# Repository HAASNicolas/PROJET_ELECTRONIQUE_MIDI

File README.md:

# PROJET_ELECTRONIQUE_MIDI
## Participants
* Lina Bachir
* Nicolas Haas
* Tanoh Koffi

## Code C
```C
int main (void)
{
  printf(C);
}
```

## Commandes github
Sous window: Dans le répertoire faire clique droit 'ouvrir un git bach', puis aller dans le bon dossier (si c'est pas déjà le cas):

Sous linux: Ouvrir un terminal, puis aller dans le bon dossier. Par exemple :
```
cd Documents/git_1A/PROJET_ELECTRONIQUE_MIDI/
```

Pour créer un nouveau répertoire git:
```
git config --global user.name "Pseudo git ou Nom Prénom"
git config --global user.email "Votre e-mail"
```
Testez
```
git clone adresse_du_git
```
Si git clone marche: Vous avez fini !
Sinon si git clone ne marche pas:
```
ssh-keygen
```
Faites Entrer plusieurs fois, puis copier l'adresse /c/....pub (example: /c/Users/user_name/.ssh/id_ed25519.pub)
```
cat adresse_pub_copié_ci_dessus
```
Copier ssh key, puis Ajouter ssh key sur github.com -> setting -> sshkey
```
git clone adresse_du_git
```

Pour récupérer les modifications distantes :
```
git pull
```

Pour pousser des modifications locales
```
git add .
git commit -m "Message à remplacer"
git push
```
# Rapport projet 
## Introduction

Notre projet consiste en la création d’un contrôleur MIDI, un dispositif électronique conçu pour interagir avec divers instruments et logiciels musicaux. Le contrôleur comporte une variété de boutons, de potentiomètres et de curseurs, offrant un contrôle précis et intuitif de nombreux aspects de la production musicale, tels que le volume, les effets, et la modulation.

La conception du contrôleur inclut l’intégration de plusieurs capteurs pour détecter les actions de l’utilisateur, qui sont ensuite traduites en signaux MIDI. Ces signaux sont transmis à un ordinateur ou un autre appareil musical via une interface MIDI, permettant un contrôle en temps réel de la musique.

Le développement de ce contrôleur MIDI inclut la mise en œuvre d’une carte électronique centrale, qui gère les signaux provenant des différents capteurs, ainsi qu’une interface de sortie pour la communication avec les appareils externes.

## objectif

L'objectif de notre projet est de concevoir un contrôleur MIDI fonctionnel et intuitif, permettant aux musiciens et aux producteurs de gérer et de manipuler leurs compositions musicales de manière fluide. 
Nous cherchons à créer un dispositif qui permette un contrôle précis et efficace des éléments clés de la production musicale, tels que le volume, les effets, et la modulation.

* Implémentation du MIDI classique

  Nous voulons une compatibilité universelle avec beaucoup d'instruments et de logiciels musicaux en adoptant le protocole MIDI standard. Notre contrôleur sera conçu pour envoyer et recevoir des messages MIDI de façon fiable, facilitant ainsi son intégration dans diverses configurations musicales.

* Support du MIDI USB via USB-C

  Notre objectif est d'incorporer une interface MIDI moderne utilisant un port USB-C, permettant une connexion simple et efficace avec des ordinateurs et autres appareils prenant en charge l'USB. Cela englobera la transmission de données MIDI ainsi que l'alimentation du contrôleur.

* Autonomie sur batterie rechargeable

  Nous planifions de développer un contrôleur fonctionnant sur une batterie rechargeable pour maximiser la portabilité et la flexibilité d'utilisation. La batterie sera rechargeable via USB-C, offrant ainsi aux utilisateurs la possibilité de jouer sans être dépendant d'une source d'alimentation fixe.

* Inspirations et benchmarking

  Nous nous baserons sur des modèles de référence tels que l'Intech Studio PBF4, le Faderfox MX12 pour l'ergonomie et l'AKAI MIDIMIX pour sa disposition efficace. Ces produits nous serviront de guide dans le développement de notre contrôleur.

* Cahier des charges:

* Planning des séances

* Schéma global du projet

## PCB 

Dans cette partie de ce rapport, nous donnerons un aperçu complet de l'architecture et des composants du PCB de ce contrôleur MIDI.
On cherchera donc ici à comprendre le rôle des composants sur ce PCB et leur disposition.
Concernant le Microcontrôleur, ici le STM 32 KBTX, il est le centre du contrôleur MIDI. Son but ici est de gérer les entrées venues des boutons et potentiomètres, de traiter ces informations et d’envoyer les messages MIDI appropriés via les interfaces MIDI ou USB.

Quant aux Régulateurs de tension, ils assurent une tension stable pour alimenter les différents composants du circuit, par exemple, fournir 5V pour le microcontrôleur et 3.3V pour certains capteurs ou circuits.

On a aussi utilisé des Condensateurs pour filtrer les signaux, déparasiter les lignes d'alimentation et stabiliser les tensions. Ils sont essentiels pour réduire le bruit électronique et maintenir la stabilité des signaux. Ils sont dispersés autour du microcontrôleur et près des régulateurs de tension, souvent à proximité des broches d'alimentation pour optimiser leur efficacité. De plus, avec les Résistances, on parviendra à Limiter le courant, ajuster les niveaux de tension et effectuer des fonctions pull-up/pull-down sur les lignes de signal, elles sont quant à elles Connectées en série avec les boutons et situées près du microcontrôleur pour les pull-ups/pull-downs.

Le Connecteur MIDI utilisé ici va servir d’interface afin de connecter le contrôleur MIDI à d'autres dispositifs MIDI. Ce connecteur permet donc la communication des données MIDI. Un autre type de connecteur utilisé est le Connecteur USB qui va Permettre la connexion du contrôleur à un ordinateur pour la transmission de données MIDI et l'alimentation.

Les Traces, Les lignes rouges et bleues sur le schéma représentent les connexions électriques entre les composants. Les rouges sont sur la couche supérieure du PCB, et les bleues sur la couche inférieure. Elles sont connectées entre les différentes couches du PCB à l’aide des Vias, qui assurent ainsi une interconnexion entre les couches du PCB. Les potentiomètres, eux, capturent les entrées de l'utilisateur. Chaque potentiomètre envoie en effet un signal spécifique au microcontrôleur.

En outre, Le microcontrôleur central gère les entrées venues des boutons et les interfaces MIDI/USB. Les régulateurs de tension, condensateurs et résistances assurent la stabilité du circuit et les connecteurs MIDI et USB permettent la communication avec d'autres dispositifs MIDI et des ordinateurs.
En résumé, lorsqu'on modifie la position d’un potentiomètre du contrôleur MIDI, le microcontrôleur détecte ce changement et identifie le potentiomètre en question. Il génère ensuite un message MIDI avec les informations appropriées (comme la note et la vélocité). Ce message est transmis soit via le connecteur MIDI DIN à d'autres appareils MIDI, soit via USB à un ordinateur.

## Résultats
Nous avons réussi à faire fonctionner la carte, et a lui faire envoyer, via l'USART, des trames MIDI correspondants aux valeurs des potentiomètres.

Voici les valeurs que renvoient un des potentiomètres linéaire et un des potentiomètres rond. C'est valeurs doivent être comprise entre 0 et 127, car en MIDI on la code sur 7 bits.
Sel est le numéro transmis aux 4 MUX analogiques.

La carte regarde en boucle la valeur des potentiomètres. Si la valeur change, alors une trame MIDI est envoyée.

Comme l'ADC fait 4 conversions à la fois, nous pouvons voir 4 trames MIDI qui ce suivent:

Chaque trame comporte 3 octets, ayant chacun leur bit de start à 0.
* Le 1er octet et l'identifiant ici 0x1A
* Le 2e est le numéro du potentiomètre ici 24
* Le 3e et dernier est la valeur du potentiomètre (ici 30) codée sur 7 bits (donc le MSB qui se situe à droite est toujours à 0)

On remarque que les curseurs sont espacés de 9 bits et d'une durée de 78us. Ce qui est en accord avec notre programme que nous avons configuré pour émettre à une vitesse de 115200 bauds.

## Code

Voici le diagramme de notre code:

## Les difficultés rencontrées

* Lors de schéma afain d'avoir les bonnes valeurs des résistances et condensateurs.
* Le routage nous a aussi appris qu'il faut mettre des composants de protections, ainsi que le BMS pour la recharge de la batterie.
* Dans le routage, qui nous ont permis d'apprendre les bonnes pratiques.
* L'USART du STM32 ne voulait pas fonctionner en Half-Duplex, on a donc dû le mettre en Asynchronous. Nous avons donc la broche TX qui ne sert à rien.
* Pour le soudage de composants CMS, car il faut être précis.

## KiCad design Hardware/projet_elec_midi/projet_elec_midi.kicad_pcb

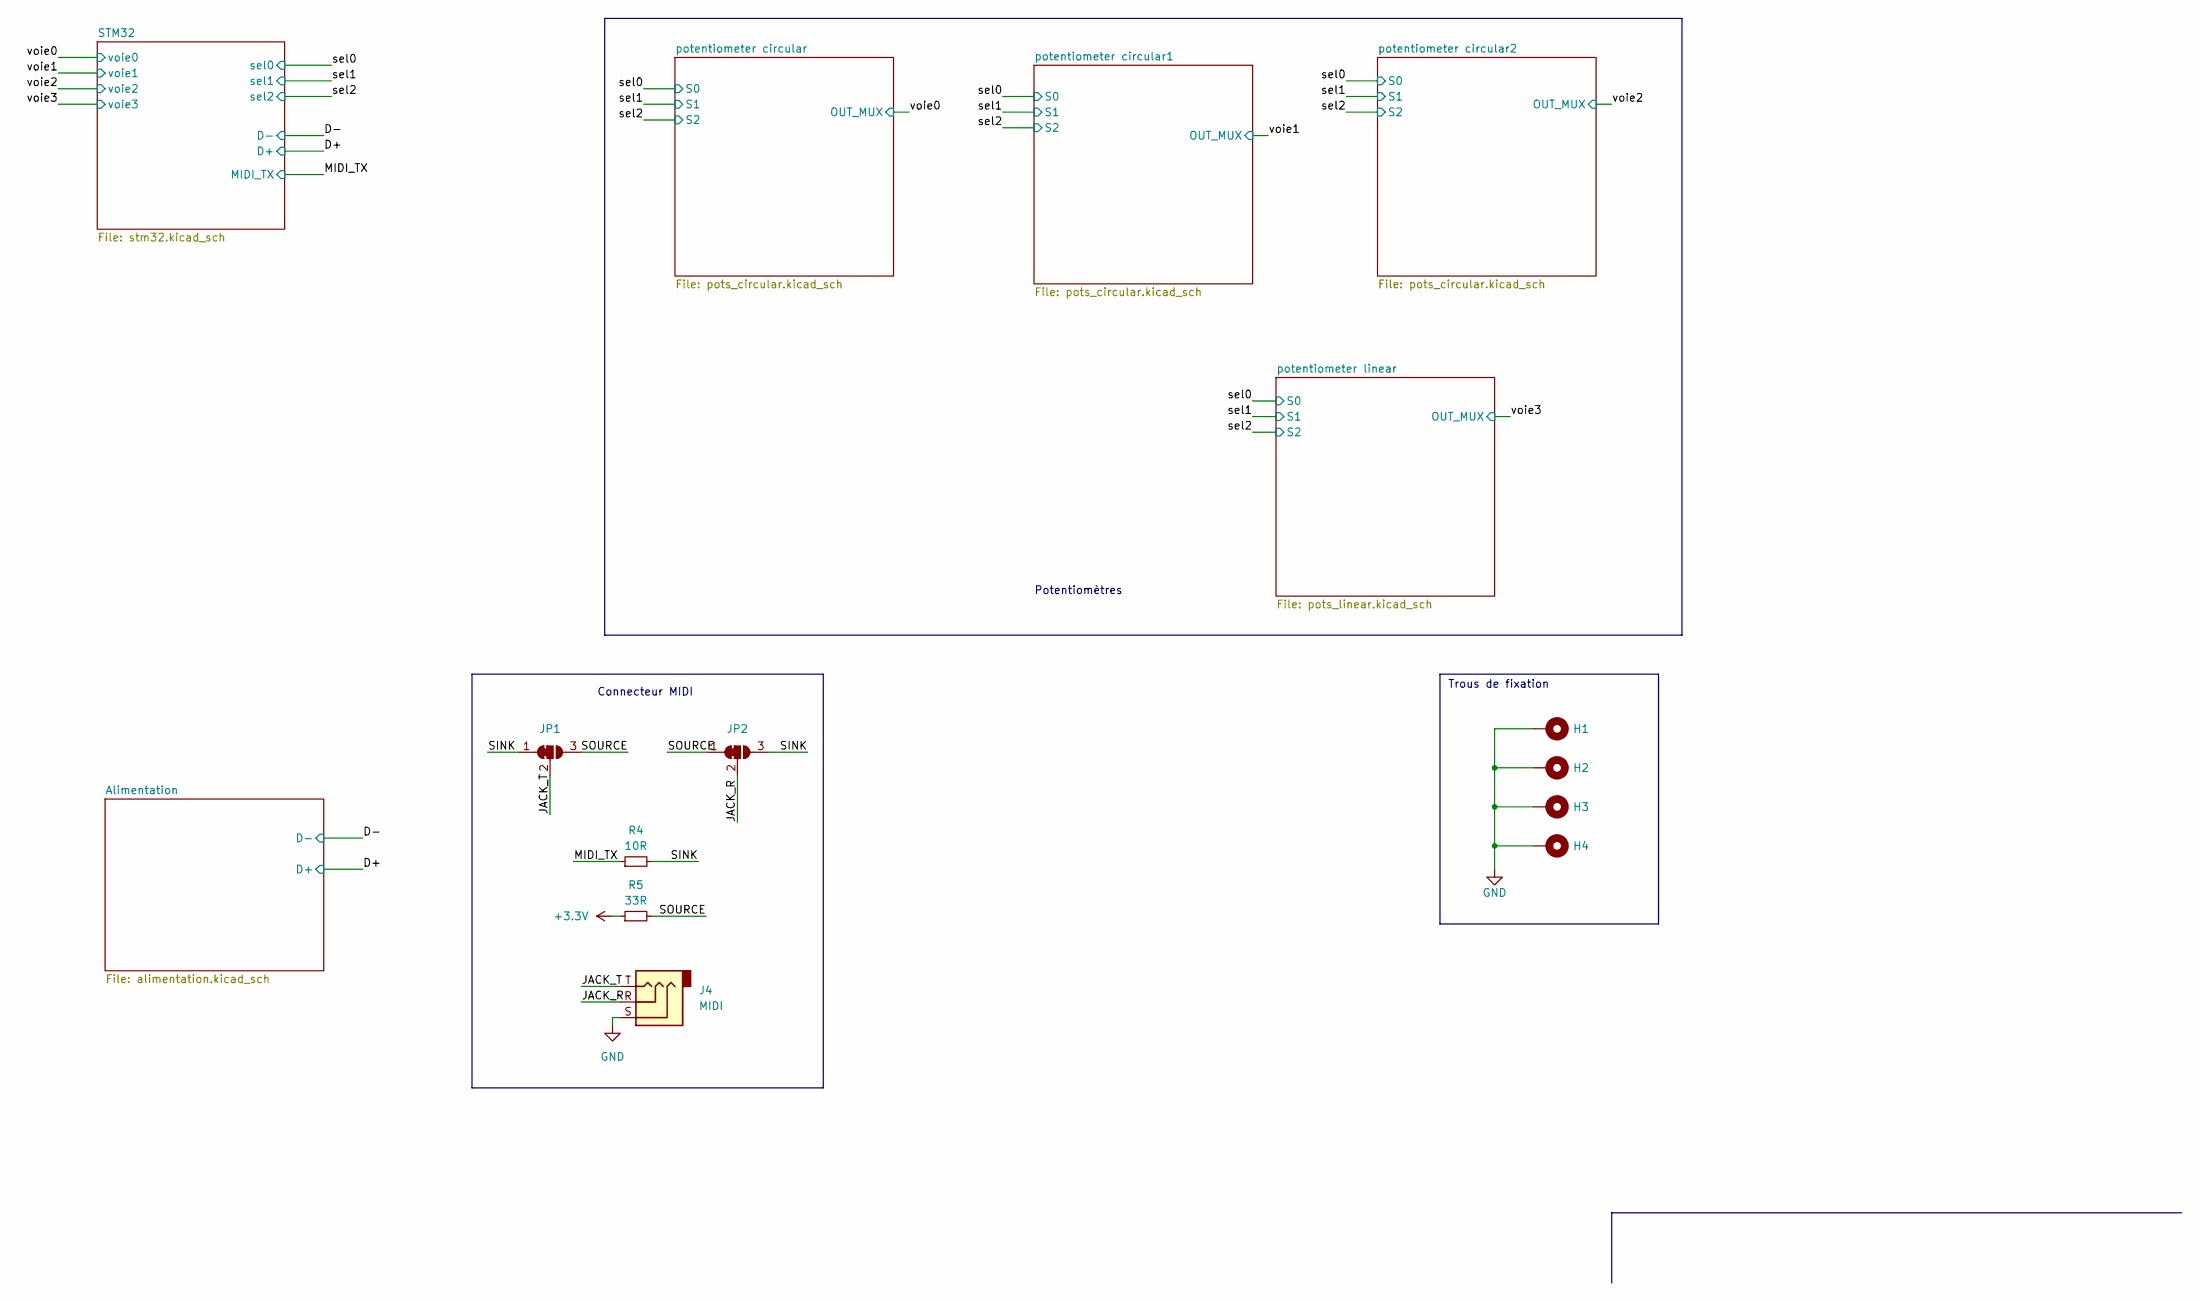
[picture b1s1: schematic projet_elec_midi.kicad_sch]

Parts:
H1, H2, H3, H4: MountingHole_Pad; MountingHole_3.2mm_M3_Pad_Via
J4: MIDI; Jack_3.5mm_CUI_SJ-3523-SMT_Horizontal
JP1, JP2: SolderJumper_3_Bridged12; SolderJumper-3_P1.3mm_Bridged12_RoundedPad1.0x1.5mm
R4: 10R; R_0805_2012Metric
R5: 33R; R_0805_2012Metric

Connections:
+3.3V: R5.1; also elsewhere on the board
/JACK_R: J4.R, JP2.2 (C)
/JACK_T: J4.T, JP1.2 (C)
/MIDI_TX: R4.1; also elsewhere on the board
/SINK: JP1.1 (A), JP2.3 (B), R4.2
/SOURCE: JP1.3 (B), JP2.1 (A), R5.2
GND: H1.1, H2.1, H3.1, H4.1, J4.S; also elsewhere on the board

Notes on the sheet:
Trous de fixation
Potentiomètres
Connecteur MIDI

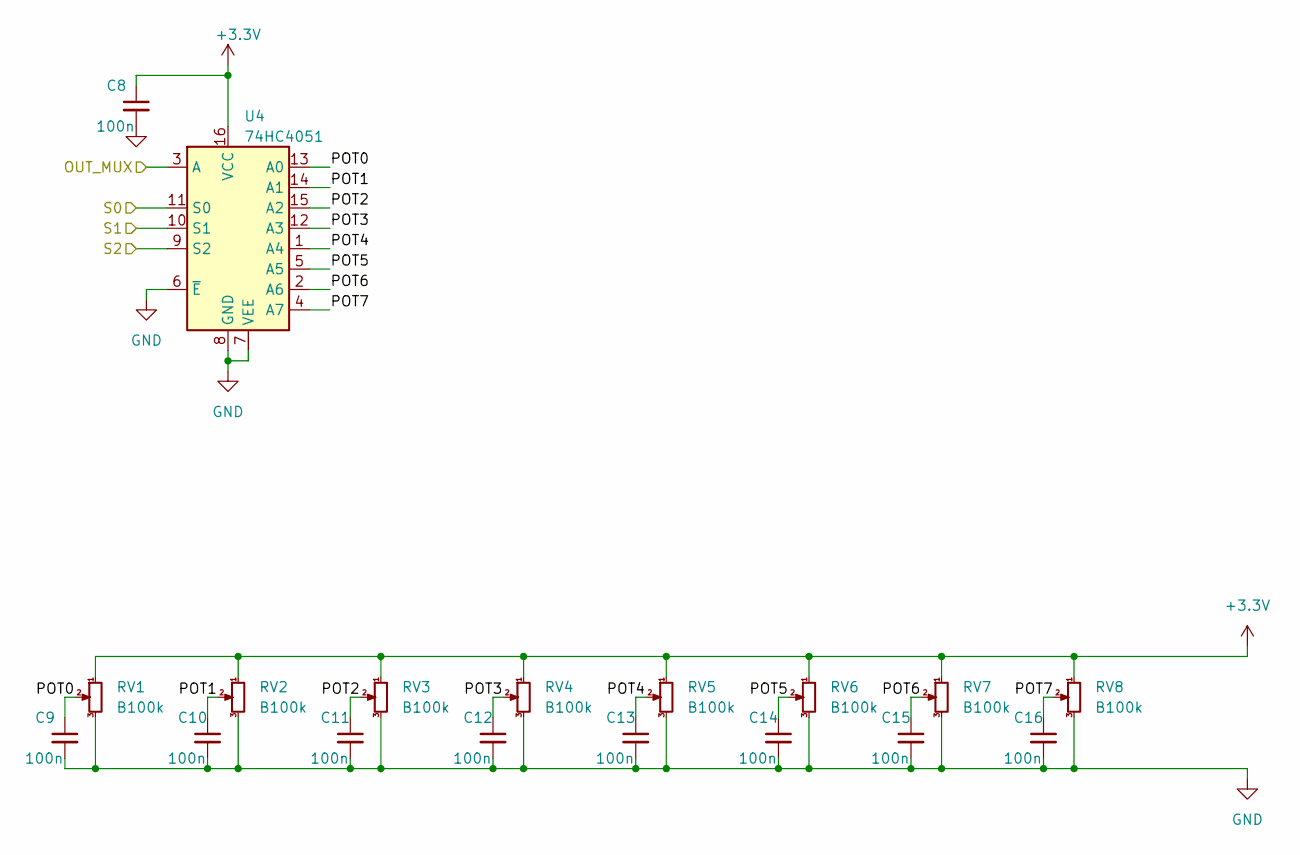
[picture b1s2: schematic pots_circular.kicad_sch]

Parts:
C8, C9, C10, C11, C12, C13, C14, C15, C16: 100n; C_0603_1608Metric
RV1, RV2, RV3, RV4, RV5, RV6, RV7, RV8: B100k; Potentiometer_Alpha_RD901F-40-00D_Single_Vertical
U4: 74HC4051; SO-16_3.9x9.9mm_P1.27mm

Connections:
+3.3V: C8.1, RV1.1, RV2.1, RV3.1, RV4.1, RV5.1, RV6.1, RV7.1, RV8.1, U4.16 (VCC); also elsewhere on the board
/potentiometer circular/POT0: C9.1, RV1.2, U4.13 (A0)
/potentiometer circular/POT1: C10.1, RV2.2, U4.14 (A1)
/potentiometer circular/POT2: C11.1, RV3.2, U4.15 (A2)
/potentiometer circular/POT3: C12.1, RV4.2, U4.12 (A3)
/potentiometer circular/POT4: C13.1, RV5.2, U4.1 (A4)
/potentiometer circular/POT5: C14.1, RV6.2, U4.5 (A5)
/potentiometer circular/POT6: C15.1, RV7.2, U4.2 (A6)
/potentiometer circular/POT7: C16.1, RV8.2, U4.4 (A7)
/sel0: U4.11 (S0); also elsewhere on the board
/sel1: U4.10 (S1); also elsewhere on the board
/sel2: U4.9 (S2); also elsewhere on the board
/voie0: U4.3 (A); also elsewhere on the board
GND: C8.2, C9.2, C10.2, C11.2, C12.2, C13.2, C14.2, C15.2, C16.2, RV1.3, RV2.3, RV3.3, RV4.3, RV5.3, RV6.3, RV7.3, RV8.3, U4.6 (~E), U4.7 (VEE), U4.8 (GND); also elsewhere on the board

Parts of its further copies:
C17, C18, C19, C20, C21, C22, C23, C24, C25, C26, C27, C28, C29, C30, C31, C32, C33, C34: 100n; C_0603_1608Metric
RV9, RV10, RV11, RV12, RV13, RV14, RV15, RV16, RV17, RV18, RV19, RV20, RV21, RV22, RV23, RV24: B100k; Potentiometer_Alpha_RD901F-40-00D_Single_Vertical
U5, U6: 74HC4051; SO-16_3.9x9.9mm_P1.27mm

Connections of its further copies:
+3.3V: C17.1, C26.1, RV9.1, RV10.1, RV11.1, RV12.1, RV13.1, RV14.1, RV15.1, RV16.1, RV17.1, RV18.1, RV19.1, RV20.1, RV21.1, RV22.1, RV23.1, RV24.1, U5.16 (VCC), U6.16 (VCC); also elsewhere on the board
/potentiometer circular1/POT0: C18.1, RV9.2, U5.13 (A0)
/potentiometer circular1/POT1: C19.1, RV10.2, U5.14 (A1)
/potentiometer circular1/POT2: C20.1, RV11.2, U5.15 (A2)
/potentiometer circular1/POT3: C21.1, RV12.2, U5.12 (A3)
/potentiometer circular1/POT4: C22.1, RV13.2, U5.1 (A4)
/potentiometer circular1/POT5: C23.1, RV14.2, U5.5 (A5)
/potentiometer circular1/POT6: C24.1, RV15.2, U5.2 (A6)
/potentiometer circular1/POT7: C25.1, RV16.2, U5.4 (A7)
/potentiometer circular2/POT0: C27.1, RV17.2, U6.13 (A0)
/potentiometer circular2/POT1: C28.1, RV18.2, U6.14 (A1)
/potentiometer circular2/POT2: C29.1, RV19.2, U6.15 (A2)
/potentiometer circular2/POT3: C30.1, RV20.2, U6.12 (A3)
/potentiometer circular2/POT4: C31.1, RV21.2, U6.1 (A4)
/potentiometer circular2/POT5: C32.1, RV22.2, U6.5 (A5)
/potentiometer circular2/POT6: C33.1, RV23.2, U6.2 (A6)
/potentiometer circular2/POT7: C34.1, RV24.2, U6.4 (A7)
/sel0: U5.11 (S0), U6.11 (S0); also elsewhere on the board
/sel1: U5.10 (S1), U6.10 (S1); also elsewhere on the board
/sel2: U5.9 (S2), U6.9 (S2); also elsewhere on the board
/voie1: U5.3 (A); also elsewhere on the board
/voie2: U6.3 (A); also elsewhere on the board
GND: C17.2, C18.2, C19.2, C20.2, C21.2, C22.2, C23.2, C24.2, C25.2, C26.2, C27.2, C28.2, C29.2, C30.2, C31.2, C32.2, C33.2, C34.2, RV9.3, RV10.3, RV11.3, RV12.3, RV13.3, RV14.3, RV15.3, RV16.3, RV17.3, RV18.3, RV19.3, RV20.3, RV21.3, RV22.3, RV23.3, RV24.3, U5.6 (~E), U5.7 (VEE), U5.8 (GND), U6.6 (~E), U6.7 (VEE), U6.8 (GND); also elsewhere on the board

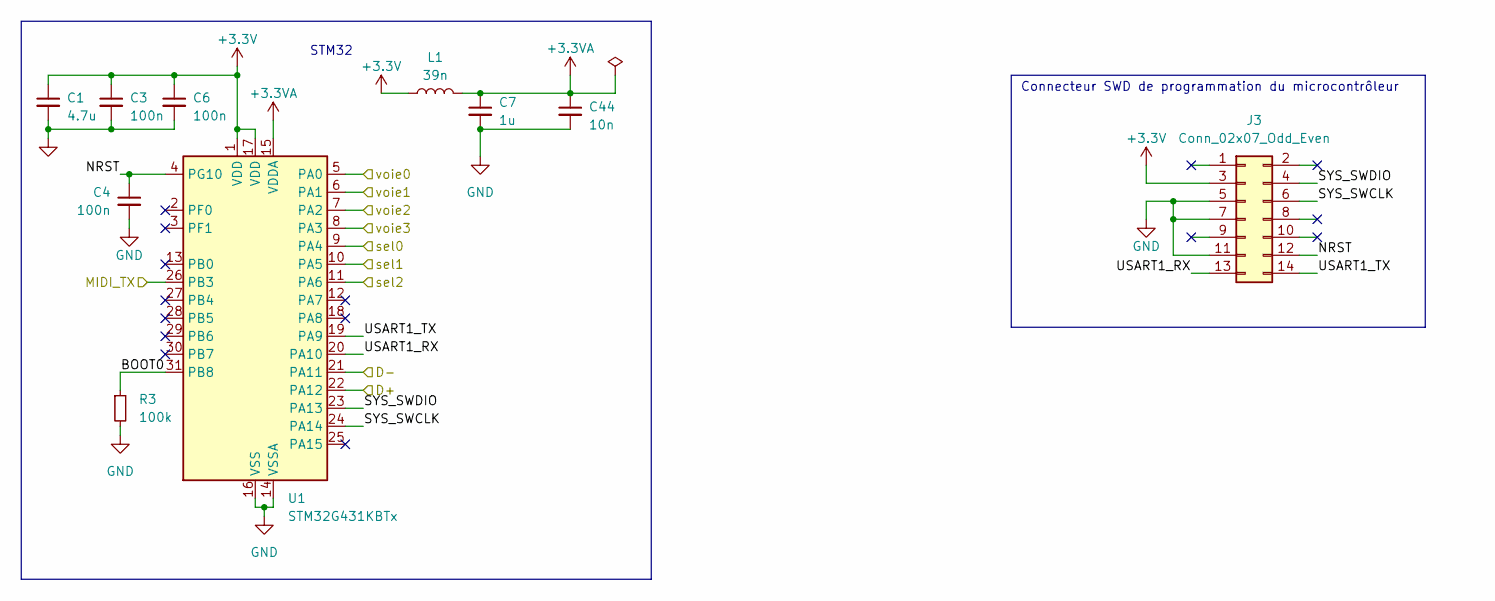
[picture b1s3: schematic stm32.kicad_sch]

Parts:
C1: 4.7u; C_0603_1608Metric
C3, C4, C6: 100n; C_0603_1608Metric
C7: 1u; C_0603_1608Metric
C44: 10n; C_0603_1608Metric
J3: Conn_02x07_Odd_Even; PinHeader_2x07_P1.27mm_Vertical_SMD
L1: 39n; L_0805_2012Metric
R3: 100k; R_0603_1608Metric
U1: STM32G431KBTx; LQFP-32_7x7mm_P0.8mm

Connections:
+3.3V: C1.1, C3.1, C6.1, J3.3, L1.1, U1.1 (VDD), U1.17 (VDD); also elsewhere on the board
+3.3VA: C7.1, C44.1, L1.2, U1.15 (VDDA)
/D+: U1.22 (PA12); also elsewhere on the board
/D-: U1.21 (PA11); also elsewhere on the board
/MIDI_TX: U1.26 (PB3); also elsewhere on the board
/STM32/BOOT0: R3.1, U1.31 (PB8)
/STM32/NRST: C4.1, J3.12, U1.4 (PG10)
/STM32/SYS_SWCLK: J3.6, U1.24 (PA14)
/STM32/SYS_SWDIO: J3.4, U1.23 (PA13)
/STM32/USART1_RX: J3.13, U1.20 (PA10)
/STM32/USART1_TX: J3.14, U1.19 (PA9)
/sel0: U1.9 (PA4); also elsewhere on the board
/sel1: U1.10 (PA5); also elsewhere on the board
/sel2: U1.11 (PA6); also elsewhere on the board
/voie0: U1.5 (PA0); also elsewhere on the board
/voie1: U1.6 (PA1); also elsewhere on the board
/voie2: U1.7 (PA2); also elsewhere on the board
/voie3: U1.8 (PA3); also elsewhere on the board
GND: C1.2, C3.2, C4.2, C6.2, C7.2, C44.2, J3.5, J3.7, J3.11, R3.2, U1.14 (VSSA), U1.16 (VSS), U1.32 (VSS); also elsewhere on the board

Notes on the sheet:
STM32
Connecteur SWD de programmation du microcontrôleur

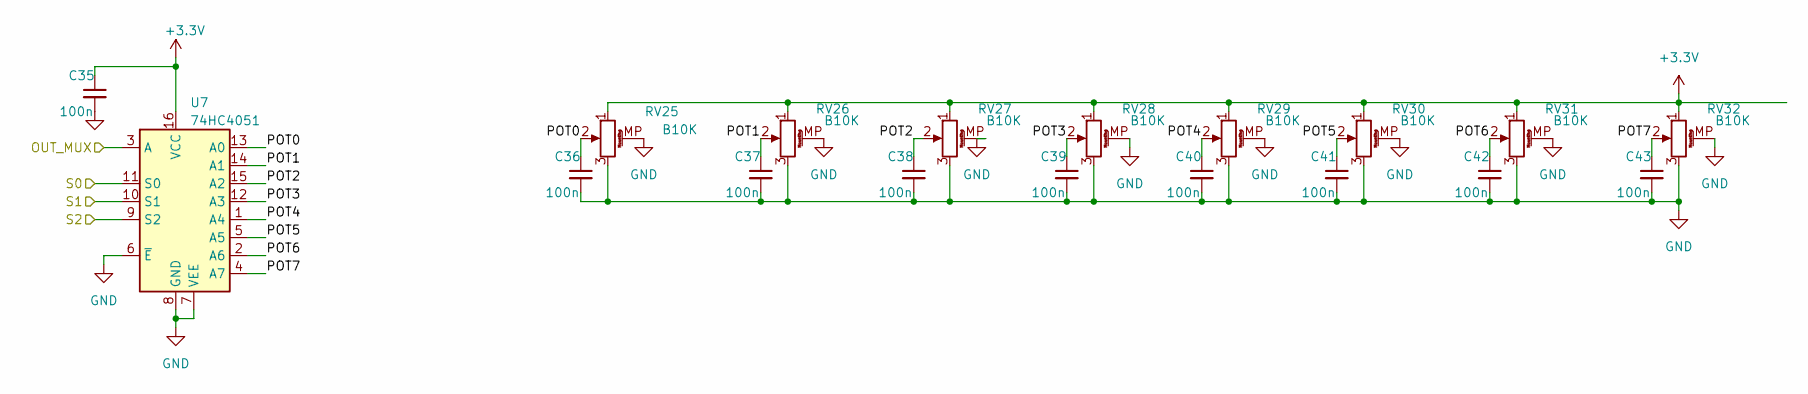
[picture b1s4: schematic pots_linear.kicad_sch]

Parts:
C35, C36, C37, C38, C39, C40, C41, C42, C43: 100n; C_0603_1608Metric
RV25, RV26, RV27, RV28, RV29, RV30, RV31, RV32: B10K; Potentiometer_Bourns_PTA3043_Single_Slide
U7: 74HC4051; SO-16_3.9x9.9mm_P1.27mm

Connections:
+3.3V: C35.1, RV25.1, RV26.1, RV27.1, RV28.1, RV29.1, RV30.1, RV31.1, RV32.1, U7.16 (VCC); also elsewhere on the board
/potentiometer linear/POT0: C36.1, RV25.2, U7.13 (A0)
/potentiometer linear/POT1: C37.1, RV26.2, U7.14 (A1)
/potentiometer linear/POT2: C38.1, RV27.2, U7.15 (A2)
/potentiometer linear/POT3: C39.1, RV28.2, U7.12 (A3)
/potentiometer linear/POT4: C40.1, RV29.2, U7.1 (A4)
/potentiometer linear/POT5: C41.1, RV30.2, U7.5 (A5)
/potentiometer linear/POT6: C42.1, RV31.2, U7.2 (A6)
/potentiometer linear/POT7: C43.1, RV32.2, U7.4 (A7)
/sel0: U7.11 (S0); also elsewhere on the board
/sel1: U7.10 (S1); also elsewhere on the board
/sel2: U7.9 (S2); also elsewhere on the board
/voie3: U7.3 (A); also elsewhere on the board
GND: C35.2, C36.2, C37.2, C38.2, C39.2, C40.2, C41.2, C42.2, C43.2, RV25.3, RV25.MP (MountPin), RV26.3, RV26.MP (MountPin), RV27.3, RV27.MP (MountPin), RV28.3, RV28.MP (MountPin), RV29.3, RV29.MP (MountPin), RV30.3, RV30.MP (MountPin), RV31.3, RV31.MP (MountPin), RV32.3, RV32.MP (MountPin), U7.6 (~E), U7.7 (VEE), U7.8 (GND); also elsewhere on the board

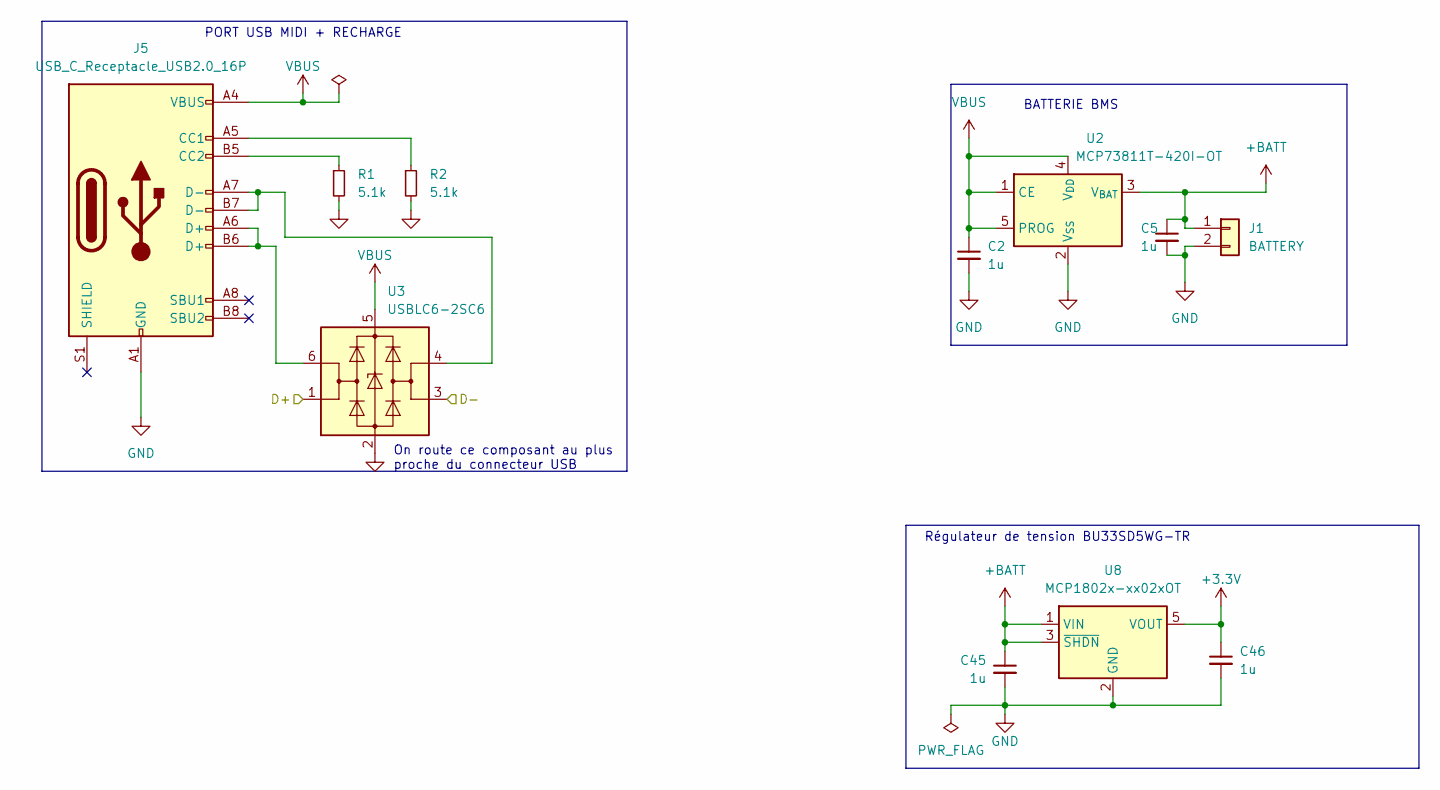
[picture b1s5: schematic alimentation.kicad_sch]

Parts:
C2, C5: 1u; C_0603_1608Metric
C45, C46: 1u; C_0603_1608Metric_Pad1.08x0.95mm_HandSolder
J1: BATTERY; JST_XH_S2B-XH-A_1x02_P2.50mm_Horizontal
J5: USB_C_Receptacle_USB2.0_16P; USB_C_Receptacle_GCT_USB4105-xx-A_16P_TopMnt_Horizontal
R1, R2: 5.1k; R_0603_1608Metric
U2: MCP73811T-420I-OT; SOT-23-5
U3: USBLC6-2SC6; SOT-23-6
U8: MCP1802x-xx02xOT; SOT-23-5

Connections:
+3.3V: C46.1, U8.5 (VOUT); also elsewhere on the board
+BATT: C5.1, C45.1, J1.1, U2.3 (V_{BAT}), U8.1 (VIN), U8.3 (~SHDN)
/D+: U3.1 (I/O1); also elsewhere on the board
/D-: U3.3 (I/O2); also elsewhere on the board
GND: C2.2, C5.2, C45.2, C46.2, J1.2, J5.A1 (GND), J5.A12 (GND), J5.B1 (GND), J5.B12 (GND), R1.2, R2.2, U2.2 (V_{SS}), U3.2 (GND), U8.2 (GND); also elsewhere on the board
unnamed: J5.A5 (CC1), R2.1
unnamed: J5.B5 (CC2), R1.1
unnamed: J5.A6 (D+), J5.B6 (D+), U3.6 (I/O1)
unnamed: J5.A7 (D-), J5.B7 (D-), U3.4 (I/O2)
VBUS: C2.1, J5.A4 (VBUS), J5.A9 (VBUS), J5.B4 (VBUS), J5.B9 (VBUS), U2.1 (CE), U2.4 (V_{DD}), U2.5 (PROG), U3.5 (VBUS)

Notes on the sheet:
Régulateur de tension BU33SD5WG-TR
On route ce composant au plus proche du connecteur USB
BATTERIE BMS
PORT USB MIDI + RECHARGE

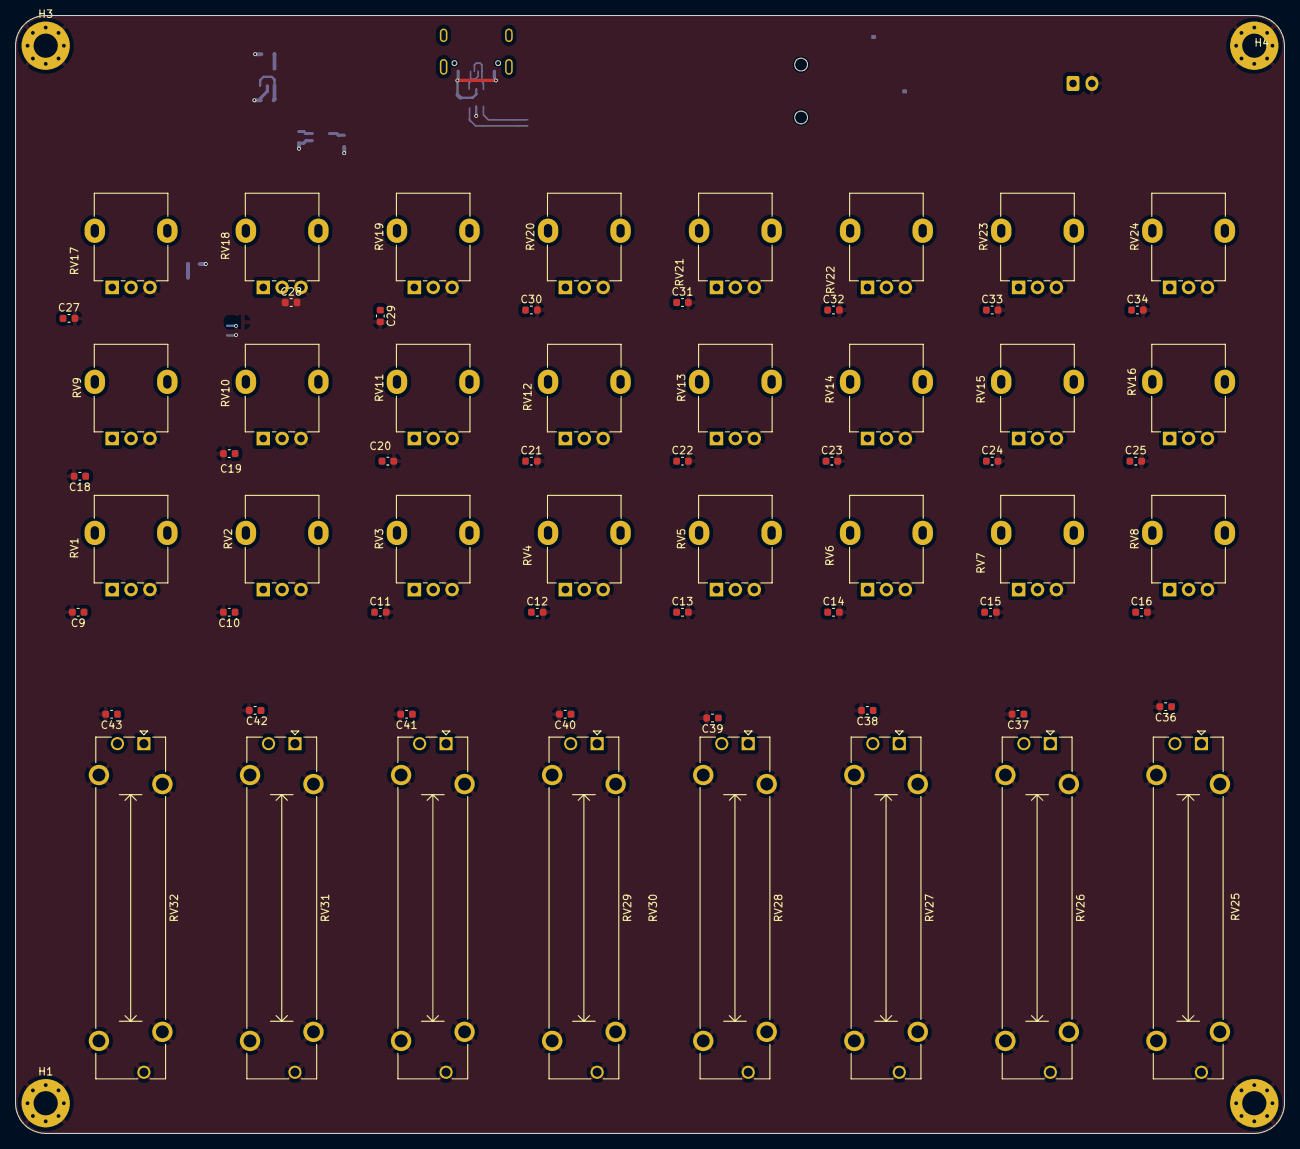
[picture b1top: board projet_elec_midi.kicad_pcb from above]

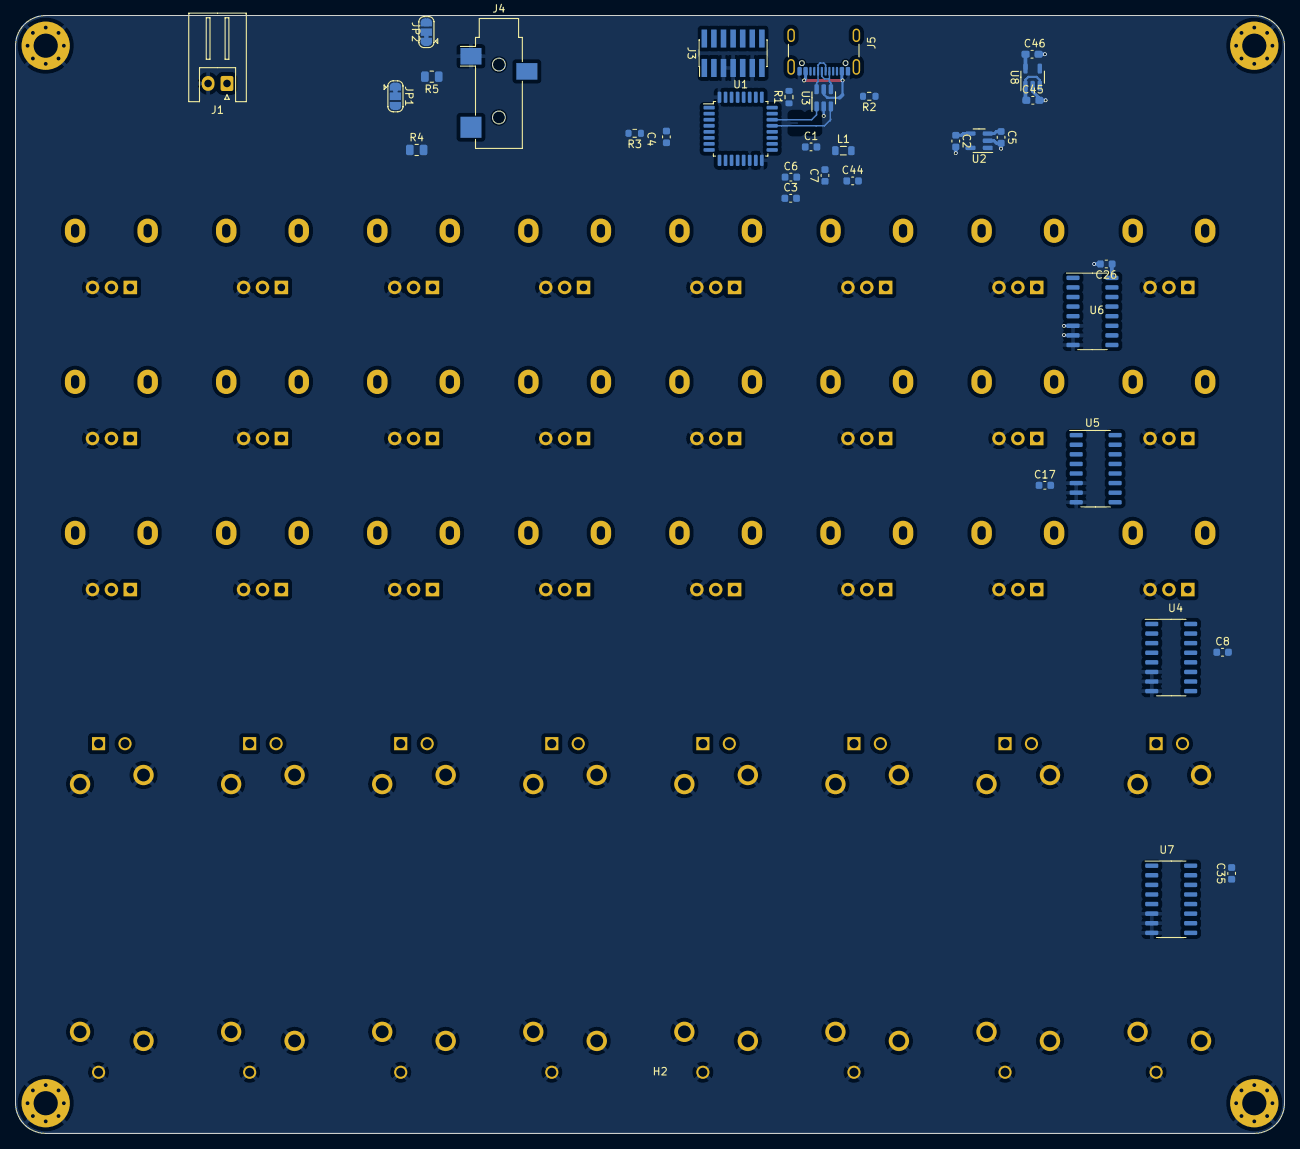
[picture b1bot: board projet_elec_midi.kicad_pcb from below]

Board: 2 copper layers, 168.0 x 148.0 mm, 102 parts (34 on the bottom side), 61 nets.

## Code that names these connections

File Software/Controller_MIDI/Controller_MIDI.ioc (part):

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Mcu.Name=STM32G431K(6-8-B)Tx
Mcu.Package=LQFP32
Mcu.UserName=STM32G431KBTx
PA0.Mode=IN1-Single-Ended
PA0.Signal=ADC1_IN1
PA1.Mode=IN2-Single-Ended
PA1.Signal=ADC1_IN2
PA10.Mode=Asynchronous
PA10.Signal=USART1_RX
PA11.Mode=Device
PA11.Signal=USB_DM
PA12.Mode=Device
PA12.Signal=USB_DP
PA13.Mode=Serial_Wire
PA13.Signal=SYS_JTMS-SWDIO
PA14.Mode=Serial_Wire
PA14.Signal=SYS_JTCK-SWCLK
PA2.Mode=IN3-Single-Ended
PA2.Signal=ADC1_IN3
PA3.Mode=IN4-Single-Ended
PA3.Signal=ADC1_IN4
PA4.Signal=GPIO_Output
PA5.Signal=GPIO_Output
PA6.Signal=GPIO_Output
PA9.Mode=Asynchronous
PA9.Signal=USART1_TX
PB3.Mode=Half_duplex(single_wire_mode)
PB3.Signal=USART2_TX
RCC.HSE_VALUE=8000000
RCC.SYSCLKFreq_VALUE=16000000
board=custom

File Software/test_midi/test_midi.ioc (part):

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Mcu.Name=STM32G431K(6-8-B)Tx
Mcu.Package=LQFP32
Mcu.UserName=STM32G431KBTx
PA0.Mode=IN1-Single-Ended
PA0.Signal=ADC1_IN1
PA1.Mode=IN2-Single-Ended
PA1.Signal=ADC1_IN2
PA10.Mode=Asynchronous
PA10.Signal=USART1_RX
PA13.Mode=Serial_Wire
PA13.Signal=SYS_JTMS-SWDIO
PA14.Mode=Serial_Wire
PA14.Signal=SYS_JTCK-SWCLK
PA2.Mode=IN3-Single-Ended
PA2.Signal=ADC1_IN3
PA3.Mode=IN4-Single-Ended
PA3.Signal=ADC1_IN4
PA4.Signal=GPIO_Output
PA5.Signal=GPIO_Output
PA6.Signal=GPIO_Output
PA9.Mode=Asynchronous
PA9.Signal=USART1_TX
RCC.HSE_VALUE=8000000
RCC.SYSCLKFreq_VALUE=64000000
RCC.SYSCLKSource=RCC_SYSCLKSOURCE_PLLCLK
board=custom

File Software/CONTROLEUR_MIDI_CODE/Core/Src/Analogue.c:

/*
 * Analogue.c
 *
 *  Created on: Apr 29, 2024
 *      Author: eleve
 */

#include <stm32g4xx_hal.h>
#include "Analogue.h"
extern ADC_HandleTypeDef hadc1;
extern TIM_HandleTypeDef htim6;

int adc_available = 0; // Indique si l'ADC à fini la conversion Analog->Digital
uint16_t adc_tab[4];
uint16_t values[32] = {0};
int sel = 0; // Sélection des 4 potentiomètres pour les MUX_Analogiques

void Analogue_init(void)
{
	edit_sel_pots();
	HAL_ADC_Start_DMA(&hadc1, (uint32_t*)adc_tab, 4); // Active l'ADC
	HAL_TIM_Base_Start(&htim6); // Appel la fonction Analogue_irq_callback() quand la conversion Analog->Digital est finie
}

void Analogue_irq_callback(void)
{
	adc_available = 1; // Indique que la conversion Analog->Digital est finie
}

void Analogue_process(void)
{
	if (adc_available == 1) // Si l'ADC a convertit la tension en numérique
	{
		printf("%u\t", sel);
		for(int itr = 0 ; itr < 4 ; itr++) // Affiche les valeurs numérique des 4 potentiomètres
		{
			int numero_potard = itr + (sel * 4);
			send_new_value(numero_potard, values[numero_potard]); // envoyer la nouvelle valeur via l'UART et l'USB
			if (values[numero_potard] != adc_tab[itr]) { // Regarde si la position du potentiomètre a changée
				values[numero_potard] = adc_tab[itr]; // Enregistre la nouvelle valeur
				printf("e");
			}
			printf("%u\t", adc_tab[itr]);
		}
		printf("\r\n");

		// Modifie les 4 potentiomètres sélectionnés
		if (sel == 7) {
			sel = 0;
		} else {
			sel += 1;
		}
		edit_sel_pots();

		adc_available = 0;
	}
}

void edit_sel_pots() { // Modifie les 4 potentiomètres sélectionnés par les MUX_Analogiques
	HAL_GPIO_WritePin(GPIOA, GPIO_PIN_4, sel & 0b1); // sel0
	HAL_GPIO_WritePin(GPIOA, GPIO_PIN_5, sel & 0b10); // sel1
	HAL_GPIO_WritePin(GPIOA, GPIO_PIN_6, sel & 0b100); // sel2
}

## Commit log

2024-02-26 first commit!
2024-02-26 Update README.md
    Ajout des noms des élèves
2024-02-26 Create hardware
2024-02-26 Create Firmeware
2024-03-04 README
2024-03-04 liste produit
2024-03-04 tri documentation
2024-03-04 multiplexeur
2024-03-04 slides-seance 1
2024-03-04 Explication de comment créer un clone git
2024-03-04 Bug fix
2024-03-04 Cloner un répertoire git
2024-03-04 Apparance
2024-03-04 Nettoyage
2024-03-04 Ajout de la batterie a achetter
2024-03-11 modifs
2024-03-11 Potentiomètres
2024-03-11 Produits a achetter
2024-03-11 Kicad
2024-03-11 lock files
2024-03-18 Kicad schematic terminée
2024-03-18 Kicad début du routage
2024-03-25 STM32
2024-03-25 software STM32
2024-03-25 delate files
2024-03-25 Routage en double face
2024-04-22 Kicad version 8 - PCB presque finit
2024-04-29 Update README.md
    Intro
2024-04-29 Code de l'ADC avec un DAN
2024-05-04 Routage de la carte fini
2024-05-13 ADC fini test MIDI UART
2024-05-27 Tous les composants
2024-05-27 Trame midi fonctionne
2024-05-27 software
2024-05-27 hardware
2024-05-28 programme final qui fonctionne
2024-05-28 valeurs des pots
2024-06-03 Add files via upload
    Results
2024-06-03 Update README.md
    valeurs des potentiomètres
2024-06-03 Rename valeurs pot lineaire et rond.png to valeurs_pot_lineaire_et_rond.png
    rename
2024-06-04 Add files via upload
    Trames MIDI
2024-06-04 Update README.md
    Trames MIDI
2024-06-04 Update README.md
    Analyse des trames MIDI
2024-06-04 Add files via upload
    Ajout d'information sur l'image
2024-06-04 Add files via upload
    Image rognée
2024-06-04 Update README.md
    vitesse de transmission
2024-06-04 Add files via upload
    planning et cahier des charges
2024-06-04 Add files via upload
    Diagramme du code
2024-06-04 Update README.md
    diagramme du code
2024-06-04 Update README.md
    Ajout du cahier des charges et du planning
2024-06-04 Add files via upload
    Schéma global du projet
2024-06-04 Update README.md
    Ajout du schéma global du projet
2024-06-04 Add files via upload
    Image du PCB final
2024-06-04 Update README.md
    image PCB
2024-06-04 Rename PBC.png to PCB.png
2024-06-04 Update README.md
    ajout des difficultés
